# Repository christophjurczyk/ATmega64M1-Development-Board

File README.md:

# ATmega64M1-Development-Board (Arduino-Compatible)

This projects brings an Arduino-compatible development board for the Atmel ATmega64M1 microcontroller. The ATmega64M1 is an 8-bit AVR RISC-based microcontroller and with the CAN capabilities widely used in the automotive industry.

The microcontroller has some additional features to the widely-used Arduino UNO:
- CAN interface
- DAC
- internal temperature sensor

With the help of ATmegaxxM1-C1 Arduino Core of thomasonw (https://github.com/thomasonw/ATmegaxxM1-C1) it is possible to work with the Arduino environment on this board. But you are also able to program the board directly via an ICSP and a dedicated programmer.

## Notes
### CAN Interface
The CAN interface can be handled by two CAN transceivers. You can choose between an isolated (ADM3053) and a non-isolated (MCP2562) CAN transceiver. If you are using the ADM3053, you have to equip the board with R6 and C12 to C15. C5 to C8 are mandatory for both configurations.

### Power Supply
You power the board via three different ways: USB, VIN (DC-Jack or pin header) or CAN interface (3: GND and 9: VCC). You can configure the power supply via the jumper JP2 and JP3 next to the DC-Jack. 
If you are using the CAN interface as power provision, you have to close the solder jumper SJ4 next to the CAN interface. **Caution:** If you are closing this jumper the grounds of the board and CAN interface are no more isolated to each other!

### Logic Level
You can run the controller with 5V or 3.3V. You can configure this via the jumper JP4 next to the DC-Jack.

# Bill of Materials (Thanks to @elasticdotventures)
Per Unit in non-isolated can bus (MCP2562 config)

### Chips:
* 1x ATMEGA64M1 IC11
* 1x FT232RL  IC4
* 1x MCP2562  U1

### Capacitors: 
* 6x smd 1206 / 3216 polar 10uf tantulum    c1,c2,c3,c4,c5,c7
* 6x smd 0805 / 2012 non-polar 100nf    c6,c8,c16,c17,c18,c19
* 2x smd 0805 / 2012 non-polar 22pf   c9,c11

### Oscillators:
* 16mhz Q1

### Voltage Regulator:
* AMS1117 LM1117IMPX-3.3 15Vin 3.3Vout 800ma SOT223	IC1    	
* AMS1117 LM1117IMPX-5.0 15Vin 3.3Vout 800ma SOT223  IC2	   

### 0805 / 2012 Resistors:
* 6x 1k r1,r2,r4,r5, r8,r9
* 1x 10k resistor    R3				
* 1x 120ohm resistor  r7

### 0805 Leds:
* 6x color your choice

### Misc: 
* 1x X1 micro USB
* 1x ISCP connector 3x2 pin header 	SV1
* 1x DC Jack - DCJ0202  J1
* 1x sw1 (reset)
* 6x surface jumpers  sj1,sj2,sj3,sj4,sj5
* 1x smd fuse 1206 f1

### Optional isolated can bus ADM3053
2x smd 1206 / 3216 polar 10uf  C12,c15						
2x smd 0805 / 2012 non-polar 100uf  c13,14   
1x 47k 0805 resistor r6

### Improved CAN terminator (replaces r7 120ohm) - coming soon!
2 x 60ohm  r7a r7b
1 x 4.7nf capacitor

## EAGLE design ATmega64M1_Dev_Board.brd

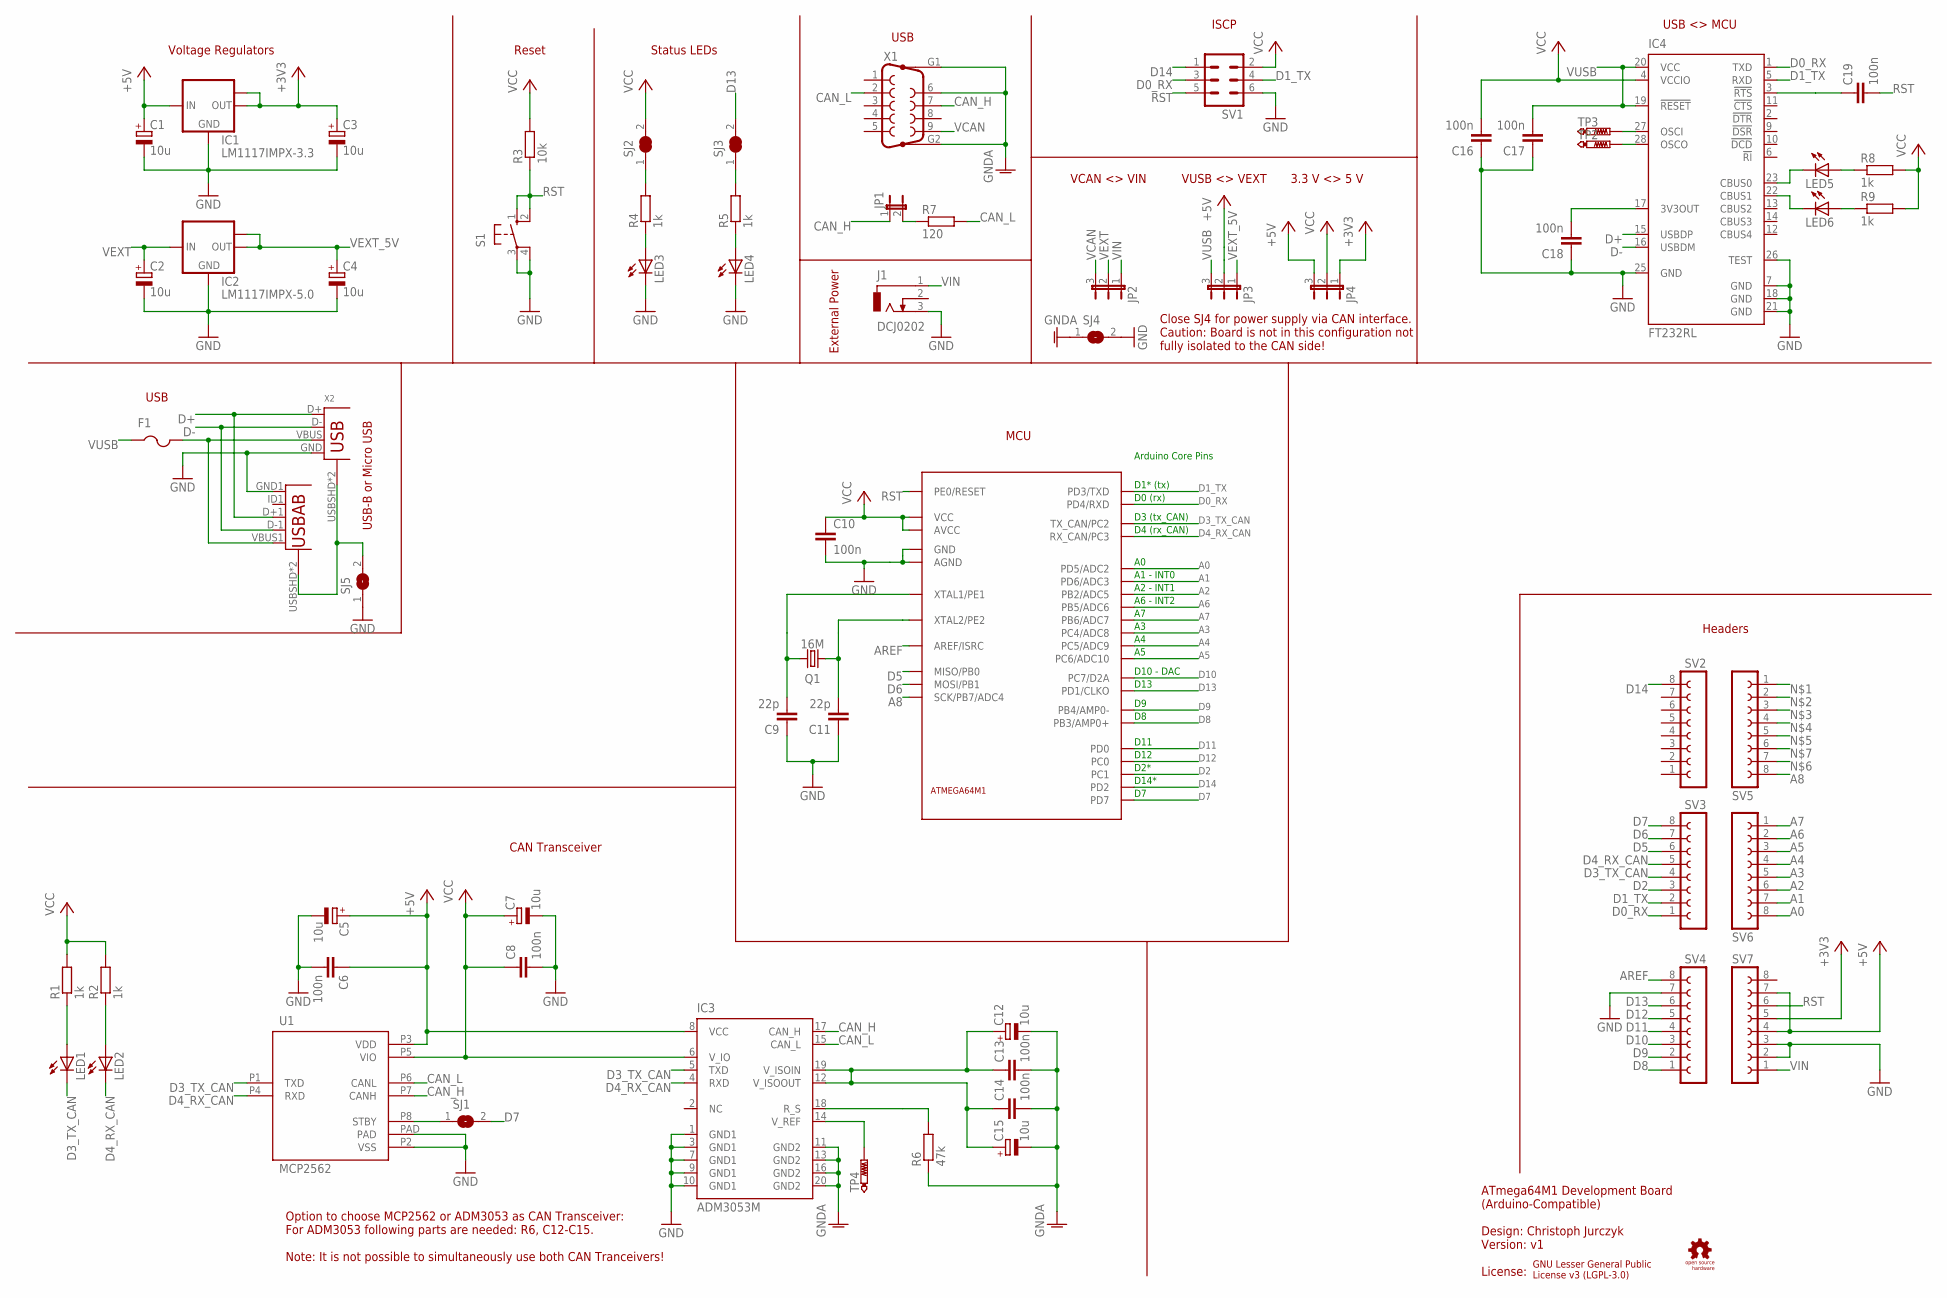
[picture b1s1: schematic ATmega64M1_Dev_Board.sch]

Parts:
C1, C2, C3, C4, C5, C7, C12, C15: 10u; A/3216-18W
C6, C8, C10, C13, C14, C16, C17, C18, C19: 100n; C0603
C9, C11: 22p; C0603
F1: PTCFUSE-1206; R1206
GOLD_ORB_SM1: OSHWLOGOLOGO8MM; OSHW_8MM
IC1: LM1117IMPX-3.3; SOT223
IC2: LM1117IMPX-5.0; SOT223
IC3: ADM3053M; SO20W
IC4: FT232RL; SSOP28
IC11: ATMEGA64M1TQFP32; QFP-32
J1: DCJ0202
JP1: JP1E; JP1
JP2, JP3, JP4: JP2E; JP2
LED1, LED2, LED3, LED4, LED5, LED6: LEDSML0805; SML0805
Q1: 16M; HC49/S
R1, R2, R4, R5, R8, R9: 1k; M0805
R3: 10k; M0805
R6: 47k; M0805
R7: 120; M0805
S1: 10-XX; B3F-10XX
SJ1, SJ4, SJ5: SJ
SJ2, SJ3: SJ_NC
SV1: ML6
SV2, SV3, SV4, SV5, SV6, SV7: FE08-1; FE08
TP2, TP3, TP4: PTR1B1,27; B1,27
U1: MCP2562; DFN3X3
U2: USB; USB-MICRO-SMD_WITHOUT_PASTE
X1: F09HP
X2: USB-B-H

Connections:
+3V3: C3.+, IC1.2 (OUT), IC1.TAB (OUT1), JP4.1, SV7.5
+5V: C1.+, C5.+, C6.1, IC1.3 (IN), IC3.8 (VCC), JP3.2, JP4.3, SV7.4, SV7.7, U1.P3 (VDD)
A0: IC11.13 (PD5/ADC2), SV6.8
A1: IC11.14 (PD6/ADC3), SV6.7
A2: IC11.16 (PB2/ADC5), SV6.6
A3: IC11.17 (PC4/ADC8), SV6.5
A4: IC11.18 (PC5/ADC9), SV6.4
A5: IC11.22 (PC6/ADC10), SV6.3
A6: IC11.26 (PB5/ADC6), SV6.2
A7: IC11.27 (PB6/ADC7), SV6.1
A8: IC11.28 (SCK/PB7/ADC4), SV5.8
AREF: IC11.21 (AREF/ISRC), SV4.8
CAN_H: IC3.17 (CAN_H), JP1.1, U1.P7 (CANH), X1.7
CAN_L: IC3.15 (CAN_L), R7.2, U1.P6 (CANL), X1.2
D0_RX: IC4.1 (TXD), IC11.12 (PD4/RXD), SV1.3, SV3.1
D1_TX: IC4.5 (RXD), IC11.2 (PD3/TXD), SV1.4, SV3.2
D2: IC11.3 (PC1), SV3.3
D3_TX_CAN: IC3.5 (TXD), IC11.6 (TX_CAN/PC2), LED1.C, SV3.4, U1.P1 (TXD)
D4_RX_CAN: IC3.4 (RXD), IC11.7 (RX_CAN/PC3), LED2.C, SV3.5, U1.P4 (RXD)
D5: IC11.8 (MISO/PB0), SV3.6
D6: IC11.9 (MOSI/PB1), SV3.7
D7: IC11.15 (PD7), SJ1.2, SV3.8
D8: IC11.23 (PB3/AMP0+), SV4.1
D9: IC11.24 (PB4/AMP0-), SV4.2
D10: IC11.25 (PC7/D2A), SV4.3
D11: IC11.29 (PD0), SV4.4
D12: IC11.30 (PC0), SV4.5
D13: IC11.32 (PD1/CLKO), SJ3.2, SV4.6
D14: IC11.1 (PD2), SV1.1, SV2.8
D+: IC4.15 (USBDP), U2.D+1 (D+), X2.D+
D-: IC4.16 (USBDM), U2.D-1 (D-), X2.D-
GND: C1.-, C2.-, C3.-, C4.-, C5.-, C6.2, C7.-, C8.2, C9.1, C10.2, C11.1, C16.1, C17.1, C18.1, IC1.1 (GND), IC2.1 (GND), IC3.1 (GND1), IC3.3 (GND1), IC3.7 (GND1), IC3.9 (GND1), IC3.10 (GND1), IC4.7 (GND), IC4.18 (GND), IC4.21 (GND), IC4.25 (GND), IC4.26 (TEST), IC11.5 (GND), IC11.20 (AGND), J1.3, LED3.C, LED4.C, S1.3, S1.4 (P1), SJ4.2, SJ5.1, SV1.6, SV4.7, SV7.2, SV7.3, U1.P2 (VSS), U1.PAD, U2.GND1 (GND), X2.GND
GNDA: C12.-, C13.2, C14.2, C15.-, IC3.11 (GND2), IC3.13 (GND2), IC3.16 (GND2), IC3.20 (GND2), R6.1, SJ4.1, X1.6, X1.G1, X1.G2
unnamed: F1.2, U2.VBUS1 (VBUS), X2.VBUS
unnamed: SJ1.1, U1.P8 (STBY)
unnamed: C12.+, C13.1, C14.1, C15.+, IC3.12 (V_ISOOUT), IC3.19 (V_ISOIN)
unnamed: IC4.27 (OSCI), TP3.TP
unnamed: C18.2, IC4.17 (3V3OUT)
unnamed: IC3.18 (R_S), R6.2
unnamed: IC4.28 (OSCO), TP2.TP
unnamed: C19.1, IC4.3 (!RTS)
unnamed: IC4.22 (CBUS1), LED6.C
unnamed: IC4.23 (CBUS0), LED5.C
unnamed: LED6.A, R9.1
unnamed: LED5.A, R8.1
unnamed: JP1.2, R7.1
unnamed: LED3.A, R4.1
unnamed: LED4.A, R5.1
unnamed: LED2.A, R2.1
unnamed: LED1.A, R1.1
unnamed: IC3.14 (V_REF), TP4.TP
unnamed: R5.2, SJ3.1
unnamed: R4.2, SJ2.1
unnamed: SJ5.2, U2.USBSHD, U2.USBSHD1 (USBSHD), X2.USBSHD, X2.USBSHD2 (USBSHD)
RST: C19.2, IC11.31 (PE0/RESET), R3.1, S1.1 (S), S1.2 (S1), SV1.5, SV7.6
VCAN: JP2.3, X1.9
VCC: C7.+, C8.1, C10.1, C16.2, IC3.6 (V_IO), IC4.4 (VCCIO), IC11.4 (VCC), IC11.19 (AVCC), JP4.2, R1.2, R2.2, R3.2, R8.2, R9.2, SJ2.2, SV1.2, U1.P5 (VIO)
VEXT: C2.+, IC2.3 (IN), JP2.2
VEXT_5V: C4.+, IC2.2 (OUT), IC2.TAB (OUT1), JP3.1
VIN: J1.1, JP2.1, SV7.1
VUSB: C17.2, F1.1, IC4.19 (!RESET), IC4.20 (VCC), JP3.3
XTAL1: C9.2, IC11.10 (XTAL1/PE1), Q1.2
XTAL2: C11.2, IC11.11 (XTAL2/PE2), Q1.1

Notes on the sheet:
D1* (tx)
D0 (rx)
D3 (tx_CAN)
D4 (rx_CAN)
A1 - INT0
A2 - INT1
A6 - INT2
D10 - DAC
D13
D11
D12
D2*
D14*
Arduino Core Pins
ISCP
VUSB <> VEXT
3.3 V <> 5 V
Option to choose MCP2562 or ADM3053 as CAN Transceiver: For ADM3053 following parts are needed: R6, C12-C15. Note: It is not possible to simultaneously use both CAN Tranceivers!
USB
External Power
Status LEDs
Reset
Voltage Regulators
USB <> MCU
MCU
Headers
CAN Transceiver
ATmega64M1 Development Board (Arduino-Compatible) Design: Christoph Jurczyk Version: v1 License:
VCAN <> VIN
USB-B or Micro USB
GNU Lesser General Public License v3 (LGPL-3.0)
Close SJ4 for power supply via CAN interface. Caution: Board is not in this configuration not fully isolated to the CAN side!

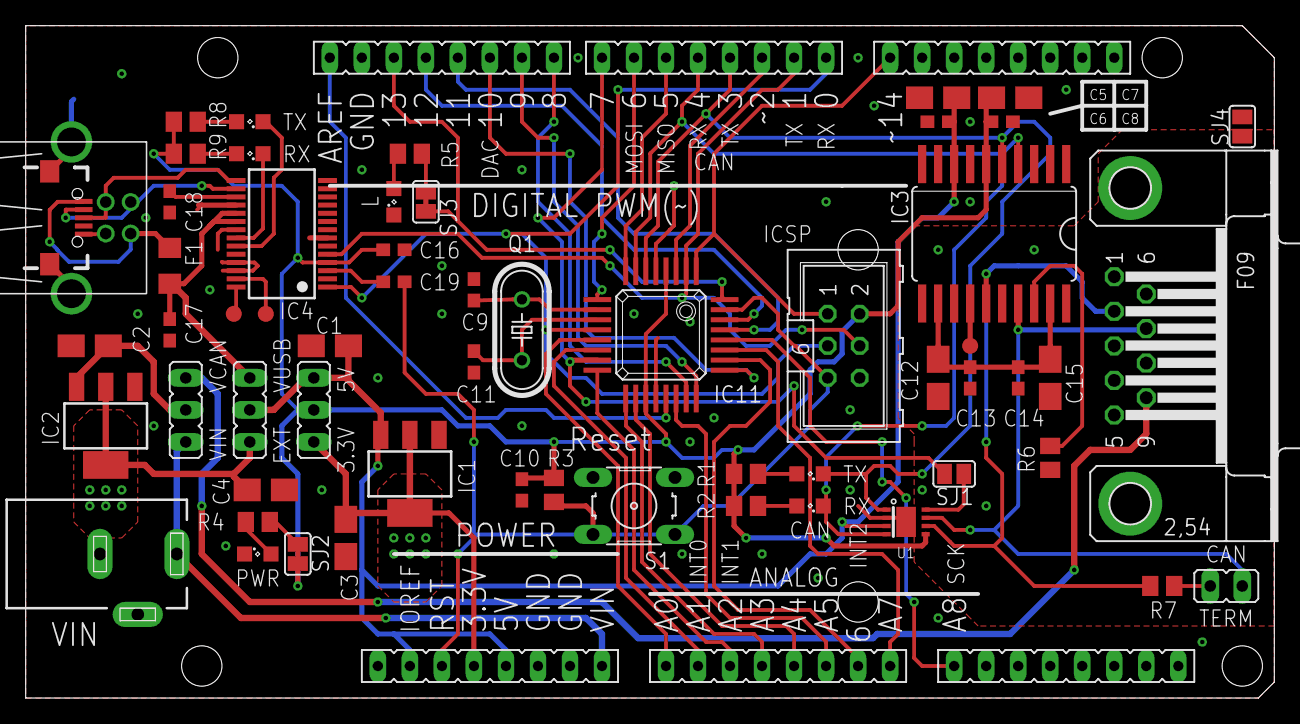
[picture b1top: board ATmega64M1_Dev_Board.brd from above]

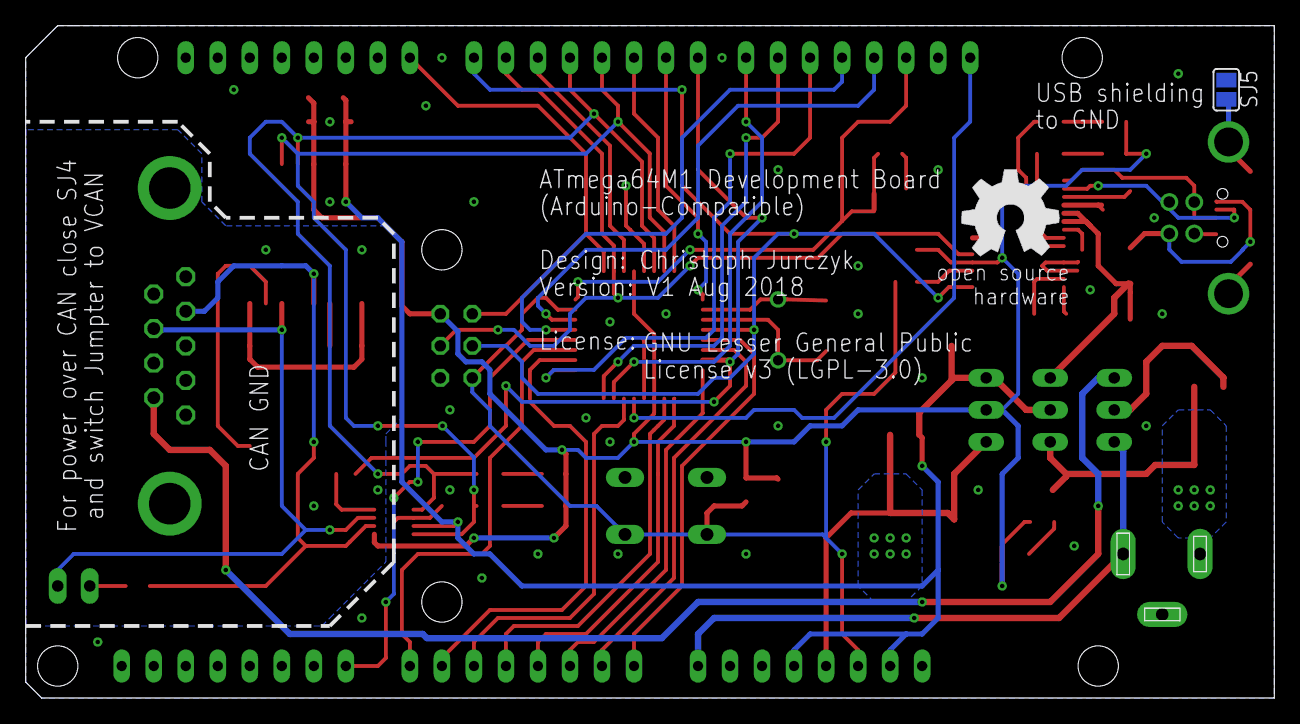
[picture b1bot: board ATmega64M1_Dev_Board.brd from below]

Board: 2 copper layers, 99.1 x 53.3 mm, 67 parts (2 on the bottom side), 63 nets.

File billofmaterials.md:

#########################################################
# Bill of Materials 
# Per Unit in non-isolated can bus (MCP2562 config)

## Chips:
* 1x ATMEGA64M1					@ 14.00
* 1x FT232RL  IC4				@ 13.00
* 1x MCP2562  U1  				@ 6.00

## Capacitors: 
* 6x smd 1206 / 3216 polar 10uf tantulum    c1,c2,c3,c4,c5,c7		  @ 0.28  
* 6x smd 0805 / 2012 non-polar 100nf    c6,c8,c16,c17,c18,c19		@ 0.08
* 2x smd 0805 / 2012 non-polar 22pf   c9,c11			0.08

## Oscillators:
* 16mhz Q1  			@ 0.20

## Voltage Regulator:
* AMS1117 LM1117IMPX-3.3 15Vin 3.3Vout 800ma SOT223	IC1    	
* AMS1117 LM1117IMPX-5.0 15Vin 3.3Vout 800ma SOT223  IC2	   

## 0805 / 2012 Resistors:
* 6x 1k r1,r2,r4,r5, r8,r9		@ 0.10
* 1x 10k resistor    R3				
* 1x 120ohm resistor  r7

## 0302 Leds:
* 3x Green LED1,LED3,LED5
* 3x Orange LED2, LED4, LED6  			@ 0.04 x 6

## Misc: 
* 1x X1 micro USB
* 1x ISCP connector 3x2 pin header 	SV1
* 1x DC Jack - DCJ0202  J1
* 1x sw1 (reset)						@ 0.05
* 6x surface jumpers  sj1,sj2,sj3,sj4,sj5
* 1x fuse - f1 1206 / 3216 1.5A 6v 		@ 0.18

#################################################
# optional isolated can bus
smd 1206 / 3216 polar 10uf  C12,c15						
smd 0805 / 2012 non-polar 100uf  c13,14   
50 x 47k resistor r6  (optional for ADM3053)

#################################################
# Improved CAN terminator (replaces r7 120ohm) - coming soon!
2 x 60ohm  r7a r7b
1 x 4.7nf capacitor



----

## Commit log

2018-08-09 Initial upload.
2018-08-09 Gerber files for JLCPCB.
2018-08-09 Minor fixes.
2018-08-09 Typo
2018-08-10 Deleted old gerber files.
2018-08-14 Fixed ICSP pin allocation.
2018-08-27 Fixed typo on silkscreen.
2018-10-07 Added some labels to board.
2020-08-19 added billofmaterials.md
2020-08-19 fix typo in readme.
2020-08-19 markdown formatting
